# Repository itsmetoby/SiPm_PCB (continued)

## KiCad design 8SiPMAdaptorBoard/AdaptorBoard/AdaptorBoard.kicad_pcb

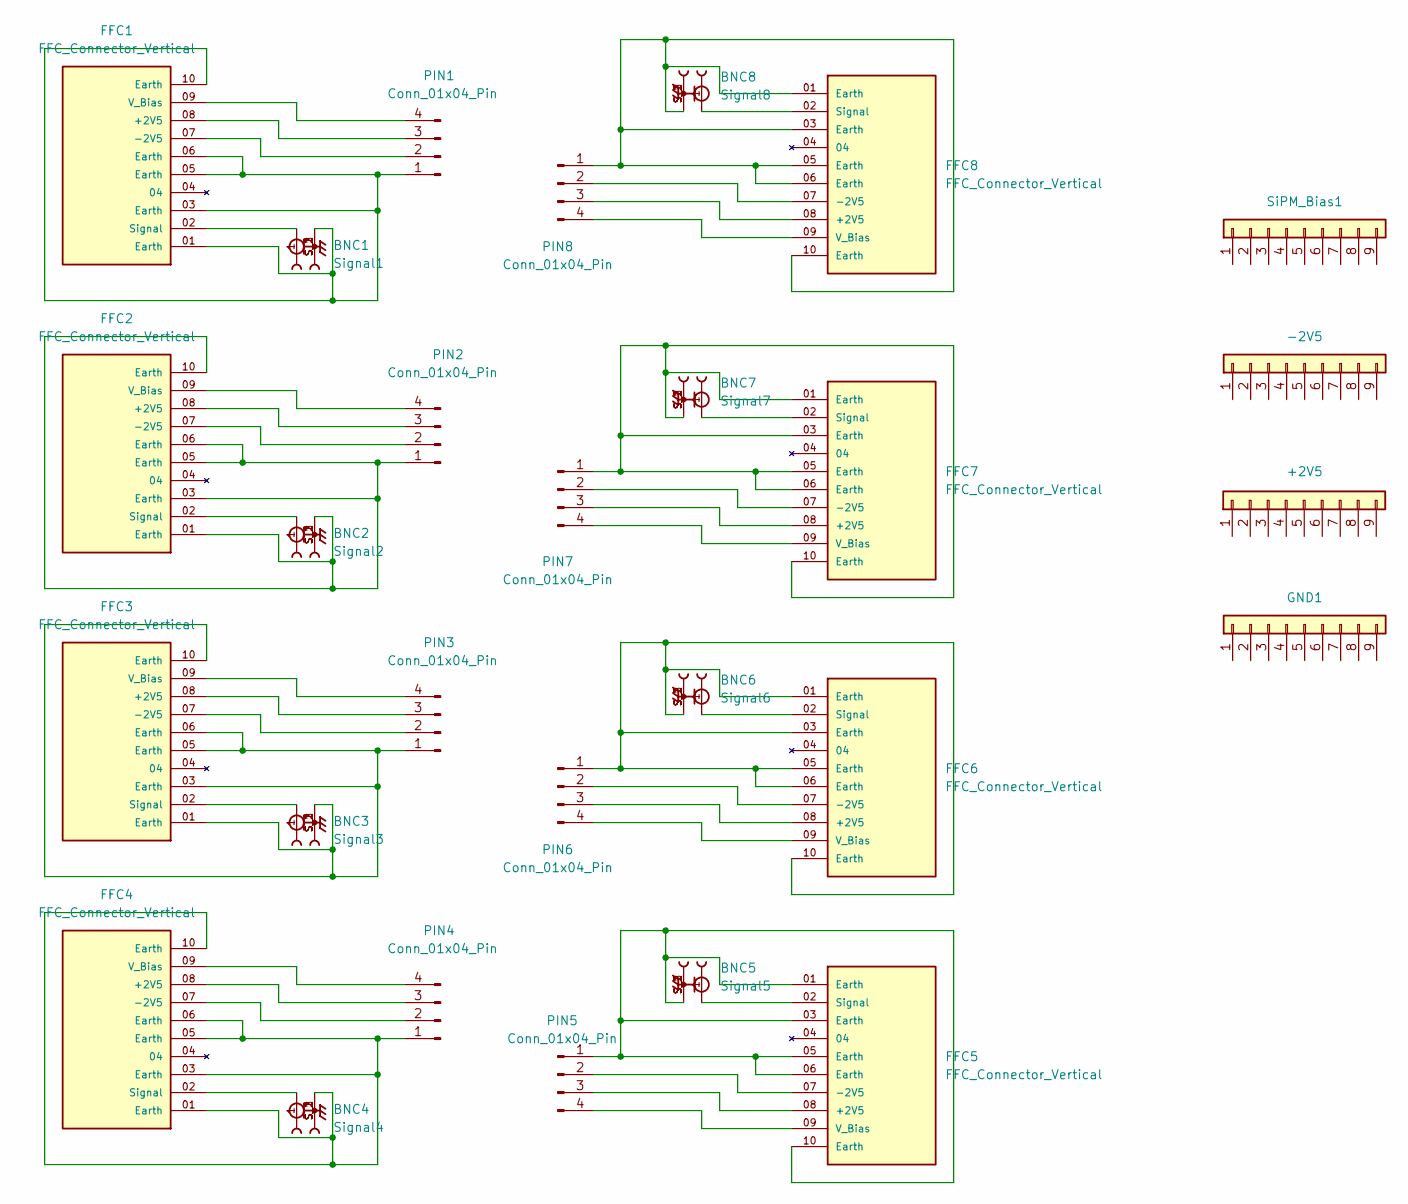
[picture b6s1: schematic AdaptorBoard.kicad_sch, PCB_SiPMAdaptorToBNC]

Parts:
+2V5: Conn_01x09; PinHeader_1x09_P1.00mm_Vertical
-2V5: Conn_01x09; PinHeader_1x09_P1.00mm_Vertical
BNC1: Signal1; SAMTEC_BNC5-J-P-GN-ST-TH2D
BNC2: Signal2; SAMTEC_BNC5-J-P-GN-ST-TH2D
BNC3: Signal3; SAMTEC_BNC5-J-P-GN-ST-TH2D
BNC4: Signal4; SAMTEC_BNC5-J-P-GN-ST-TH2D
BNC5: Signal5; SAMTEC_BNC5-J-P-GN-ST-TH2D
BNC6: Signal6; SAMTEC_BNC5-J-P-GN-ST-TH2D
BNC7: Signal7; SAMTEC_BNC5-J-P-GN-ST-TH2D
BNC8: Signal8; SAMTEC_BNC5-J-P-GN-ST-TH2D
FFC1, FFC2, FFC3, FFC4, FFC5, FFC6, FFC7, FFC8: FFC_Connector_Vertical; SAMTEC_ZF5S-10-03-T-WT
GND1: Conn_01x09; PinHeader_1x09_P1.00mm_Vertical
PIN1, PIN2, PIN3, PIN4, PIN5, PIN6, PIN7, PIN8: Conn_01x04_Pin; PinHeader_1x04_P1.00mm_Vertical
SiPM_Bias1: Conn_01x09; PinHeader_1x09_P1.00mm_Vertical

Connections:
unnamed: FFC1.08 (+2V5), PIN1.3
unnamed: FFC1.07 (-2V5), PIN1.2
unnamed: BNC1.1, FFC1.02 (Signal)
unnamed: FFC1.09 (V_Bias), PIN1.4
unnamed: FFC2.08 (+2V5), PIN2.3
unnamed: FFC2.07 (-2V5), PIN2.2
unnamed: BNC2.1, FFC2.02 (Signal)
unnamed: FFC2.09 (V_Bias), PIN2.4
unnamed: FFC3.08 (+2V5), PIN3.3
unnamed: FFC3.07 (-2V5), PIN3.2
unnamed: BNC3.1, FFC3.02 (Signal)
unnamed: FFC3.09 (V_Bias), PIN3.4
unnamed: FFC4.08 (+2V5), PIN4.3
unnamed: FFC4.07 (-2V5), PIN4.2
unnamed: BNC4.1, FFC4.02 (Signal)
unnamed: FFC4.09 (V_Bias), PIN4.4
unnamed: FFC5.08 (+2V5), PIN5.3
unnamed: FFC5.07 (-2V5), PIN5.2
unnamed: BNC5.1, FFC5.02 (Signal)
unnamed: FFC5.09 (V_Bias), PIN5.4
unnamed: FFC6.08 (+2V5), PIN6.3
unnamed: FFC6.07 (-2V5), PIN6.2
unnamed: BNC6.1, FFC6.02 (Signal)
unnamed: FFC6.09 (V_Bias), PIN6.4
unnamed: FFC7.08 (+2V5), PIN7.3
unnamed: FFC7.07 (-2V5), PIN7.2
unnamed: BNC7.1, FFC7.02 (Signal)
unnamed: FFC7.09 (V_Bias), PIN7.4
unnamed: FFC8.08 (+2V5), PIN8.3
unnamed: FFC8.07 (-2V5), PIN8.2
unnamed: BNC8.1, FFC8.02 (Signal)
unnamed: FFC8.09 (V_Bias), PIN8.4
unnamed: BNC1.S_1, BNC1.S_2, BNC1.S_3, FFC1.01 (Earth), FFC1.03 (Earth), FFC1.05 (Earth), FFC1.06 (Earth), FFC1.10 (Earth), PIN1.1
unnamed: BNC2.S_1, BNC2.S_2, BNC2.S_3, FFC2.01 (Earth), FFC2.03 (Earth), FFC2.05 (Earth), FFC2.06 (Earth), FFC2.10 (Earth), PIN2.1
unnamed: BNC3.S_1, BNC3.S_2, BNC3.S_3, FFC3.01 (Earth), FFC3.03 (Earth), FFC3.05 (Earth), FFC3.06 (Earth), FFC3.10 (Earth), PIN3.1
unnamed: BNC4.S_1, BNC4.S_2, BNC4.S_3, FFC4.01 (Earth), FFC4.03 (Earth), FFC4.05 (Earth), FFC4.06 (Earth), FFC4.10 (Earth), PIN4.1
unnamed: BNC5.S_1, BNC5.S_2, BNC5.S_3, FFC5.01 (Earth), FFC5.03 (Earth), FFC5.05 (Earth), FFC5.06 (Earth), FFC5.10 (Earth), PIN5.1
unnamed: BNC6.S_1, BNC6.S_2, BNC6.S_3, FFC6.01 (Earth), FFC6.03 (Earth), FFC6.05 (Earth), FFC6.06 (Earth), FFC6.10 (Earth), PIN6.1
unnamed: BNC7.S_1, BNC7.S_2, BNC7.S_3, FFC7.01 (Earth), FFC7.03 (Earth), FFC7.05 (Earth), FFC7.06 (Earth), FFC7.10 (Earth), PIN7.1
unnamed: BNC8.S_1, BNC8.S_2, BNC8.S_3, FFC8.01 (Earth), FFC8.03 (Earth), FFC8.05 (Earth), FFC8.06 (Earth), FFC8.10 (Earth), PIN8.1

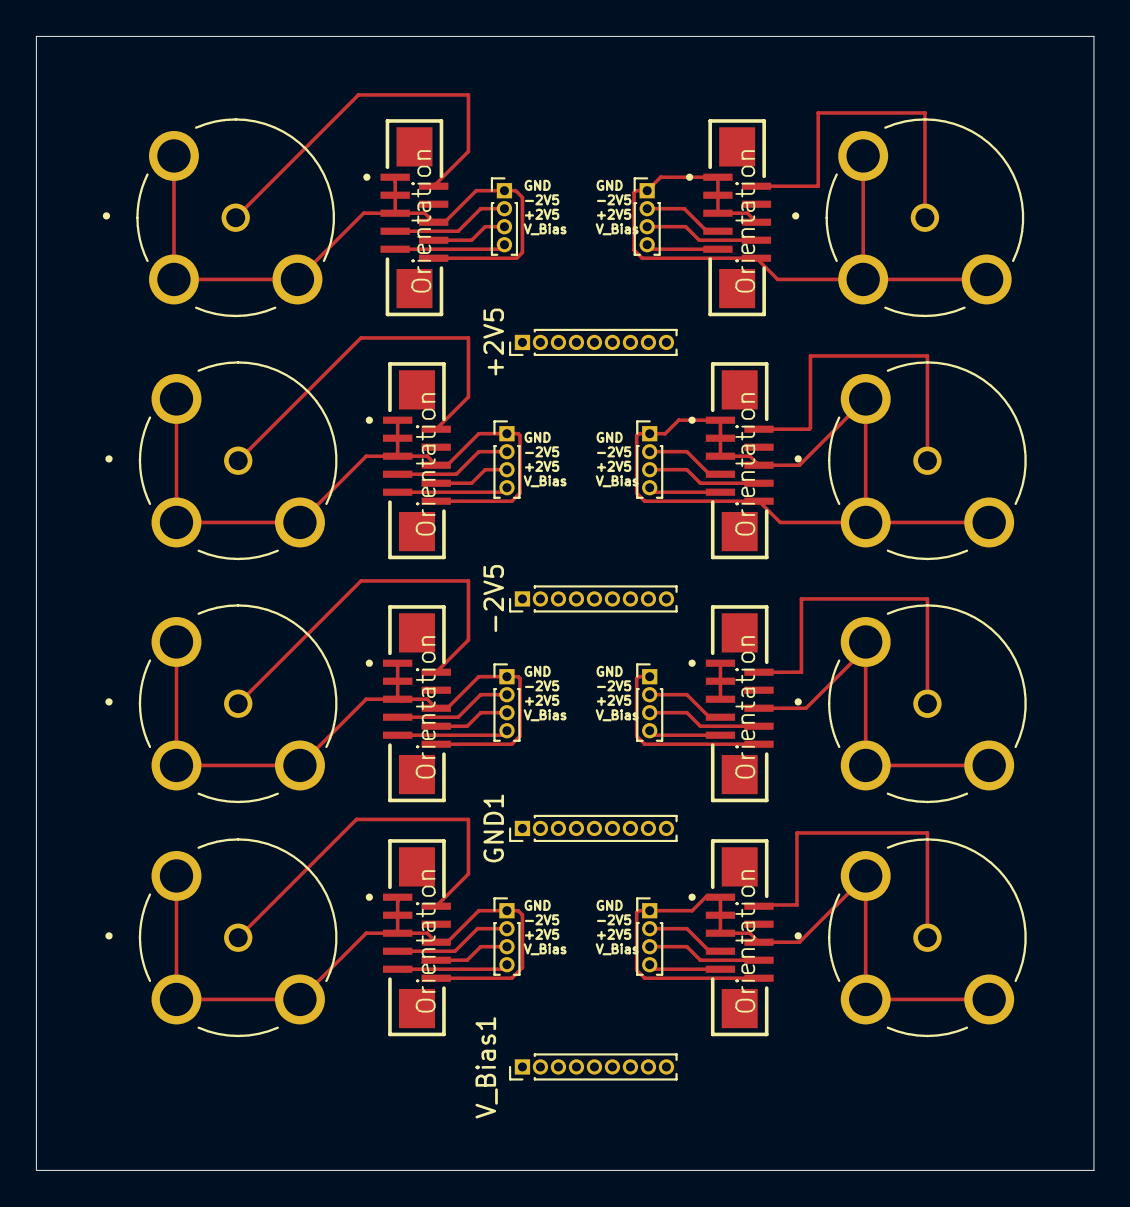
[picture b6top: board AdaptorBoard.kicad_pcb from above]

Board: 2 copper layers, 58.8 x 63.0 mm, 28 parts (0 on the bottom side), 40 nets.

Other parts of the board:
V_Bias1: Conn_01x09; PinHeader_1x09_P1.00mm_Vertical

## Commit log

2024-10-04 add +/- 2.5V "bypass cap"
    add +/- 2.5V "bypass cap"
    add res to V+ input
    add feedback cap
2024-10-05 Backlink to CADLAB.io has been added.
2024-10-05 change footprint of some res cap
2024-10-05 change to 2 opamp
    add connector
    change to OPA2354
    done layout as 2 layers
2024-10-06 add top fill, smaller font, SiPM hole
2024-10-08 1 Amp, flex , redesign
2024-10-09 ran through design rule
2024-10-14 gerber to JLC
2024-12-23 extended SiPM section, 4 mirrored footprints.
2025-03-26 Update SiPM_Adaptor_Design
2025-03-26 Update on the PCB board
2025-03-26 More update on adaptor board
2025-03-26 More update
2025-03-29 fix soldermask on SiPM, change silkscreen
2025-03-29 add gerber to JLC
2025-03-29 fix drill files
2025-03-30 A second adaptor board
2025-03-30 Update LEMO version
2025-03-31 More LEMO adaptor design
2025-03-31 add EM shield btm
2025-04-01 Update LEMOAdaptorBoard4 for horizontal FFC connector
2025-04-01 Some more update
2025-04-03 re-rount traces to pass JLC DFM
2025-04-03 move power inward, add text description
2025-04-16 Update stuff
2026-02-03 update op-amp and SiPM
2026-02-04 update first design
2026-03-22 create new design3
